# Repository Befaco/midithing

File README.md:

# MIDI Thing v2.2
Firmware for the [Befaco](http://befaco.org) Eurorack MIDI module (MIDI Thing).

## Requirements
You need Arduino >= 1.6.3. 

Additionally you will need the following libraries installed (see the [Arduino Guide](https://www.arduino.cc/en/Guide/Libraries) on how to do this):

* [Bounce2](https://github.com/thomasfredericks/Bounce2) 
* [mcp4728](https://storage.googleapis.com/google-code-archive-downloads/v2/code.google.com/neuroelec/mcp4728_library_v1.3_for_Arduino_1.0.zip)

The [MIDI library](https://github.com/FortySevenEffects/arduino_midi_library) (5.0.2) is bundled in `firmware/src/MIDI`, with a fix for a parser lockup that is not in any upstream release. No need to install it.

## bug fix

- Fixed Retrigger issues
- Fixed Perc trigger note error.

## Uploading the firmware

1. Get an ICSP Programmer 
We normally use an USBasp programmer like this one https://www.ebay.com/itm/USBASP-USB-ISP-Programmer-for-Atmel-AVR-ATMega328-ATMega32U4-Arduino-/322662323277

2. Download Arduino IDE
Go to the official Arduino website https://www.arduino.cc/en/Main/Software and download the latest version of Arduino IDE for your operating system and install it.

3. Download the firmware 
Go to https://github.com/Befaco/midithing and press "clone or download" to download the repository to your computer. Extract the zip file and copy "firmware" folder to your sketchbook folder. 

4. Install the libraries
Download the libraries from Library manager (Bounce2) and install them following the instructions from this link https://www.arduino.cc/en/Guide/Libraries
Keep in mind MCP library must be installed from the following link. Do not use library manager one:
 https://code.google.com/archive/p/neuroelec/downloads 
 
5. Connecting the module
Connect the programmer to the ICSP conector in the back of the module. Pay special attention to the pinout when you plug the module. You can check this link for more information about ICSP https://www.arduino.cc/en/Tutorial/ArduinoISP

6. Upgrading
Press "Open" and search the file "firmware.ino" located on the "firmware" folder. Select "Tools > Board > Arduino/Genuino Uno". Go to "Sketch" and hit "Upload using programmer".

If everything goes well you should see a "Done uploading" message in a few seconds. If something happens during the upgrade, check your Arduino settings following the instructions of this link https://www.arduino.cc/en/Guide/Troubleshooting

## Credits

MIDI Thing firmware v1 was coded with love by Sergio Retamero:
sergio.retamero@gmail.com

Performance boost, bug fixing and extra awesomeness by Jeremy Bernstein:
jeremy.d.bernstein@googlemail.com

Firmware v2 coding:

Quad Polyphonic modes were implemented by Jeremy Bernstein.

New configuration system, duophonic modes implementation, clock modes, a touch of beauty to the interface and a gazillion little details no living person could ever imagine by Alberto "Numeríco" Navarro:
albertonafu@gmail.com 

Calibration method inspired on Mutable instruments CVpal.

Thanks to everyone that took the time to finger point bugs, provide feedback and made loads of  suggestions. Special thanks to Jonatan "Jessica Fletcher" Bernabeu.

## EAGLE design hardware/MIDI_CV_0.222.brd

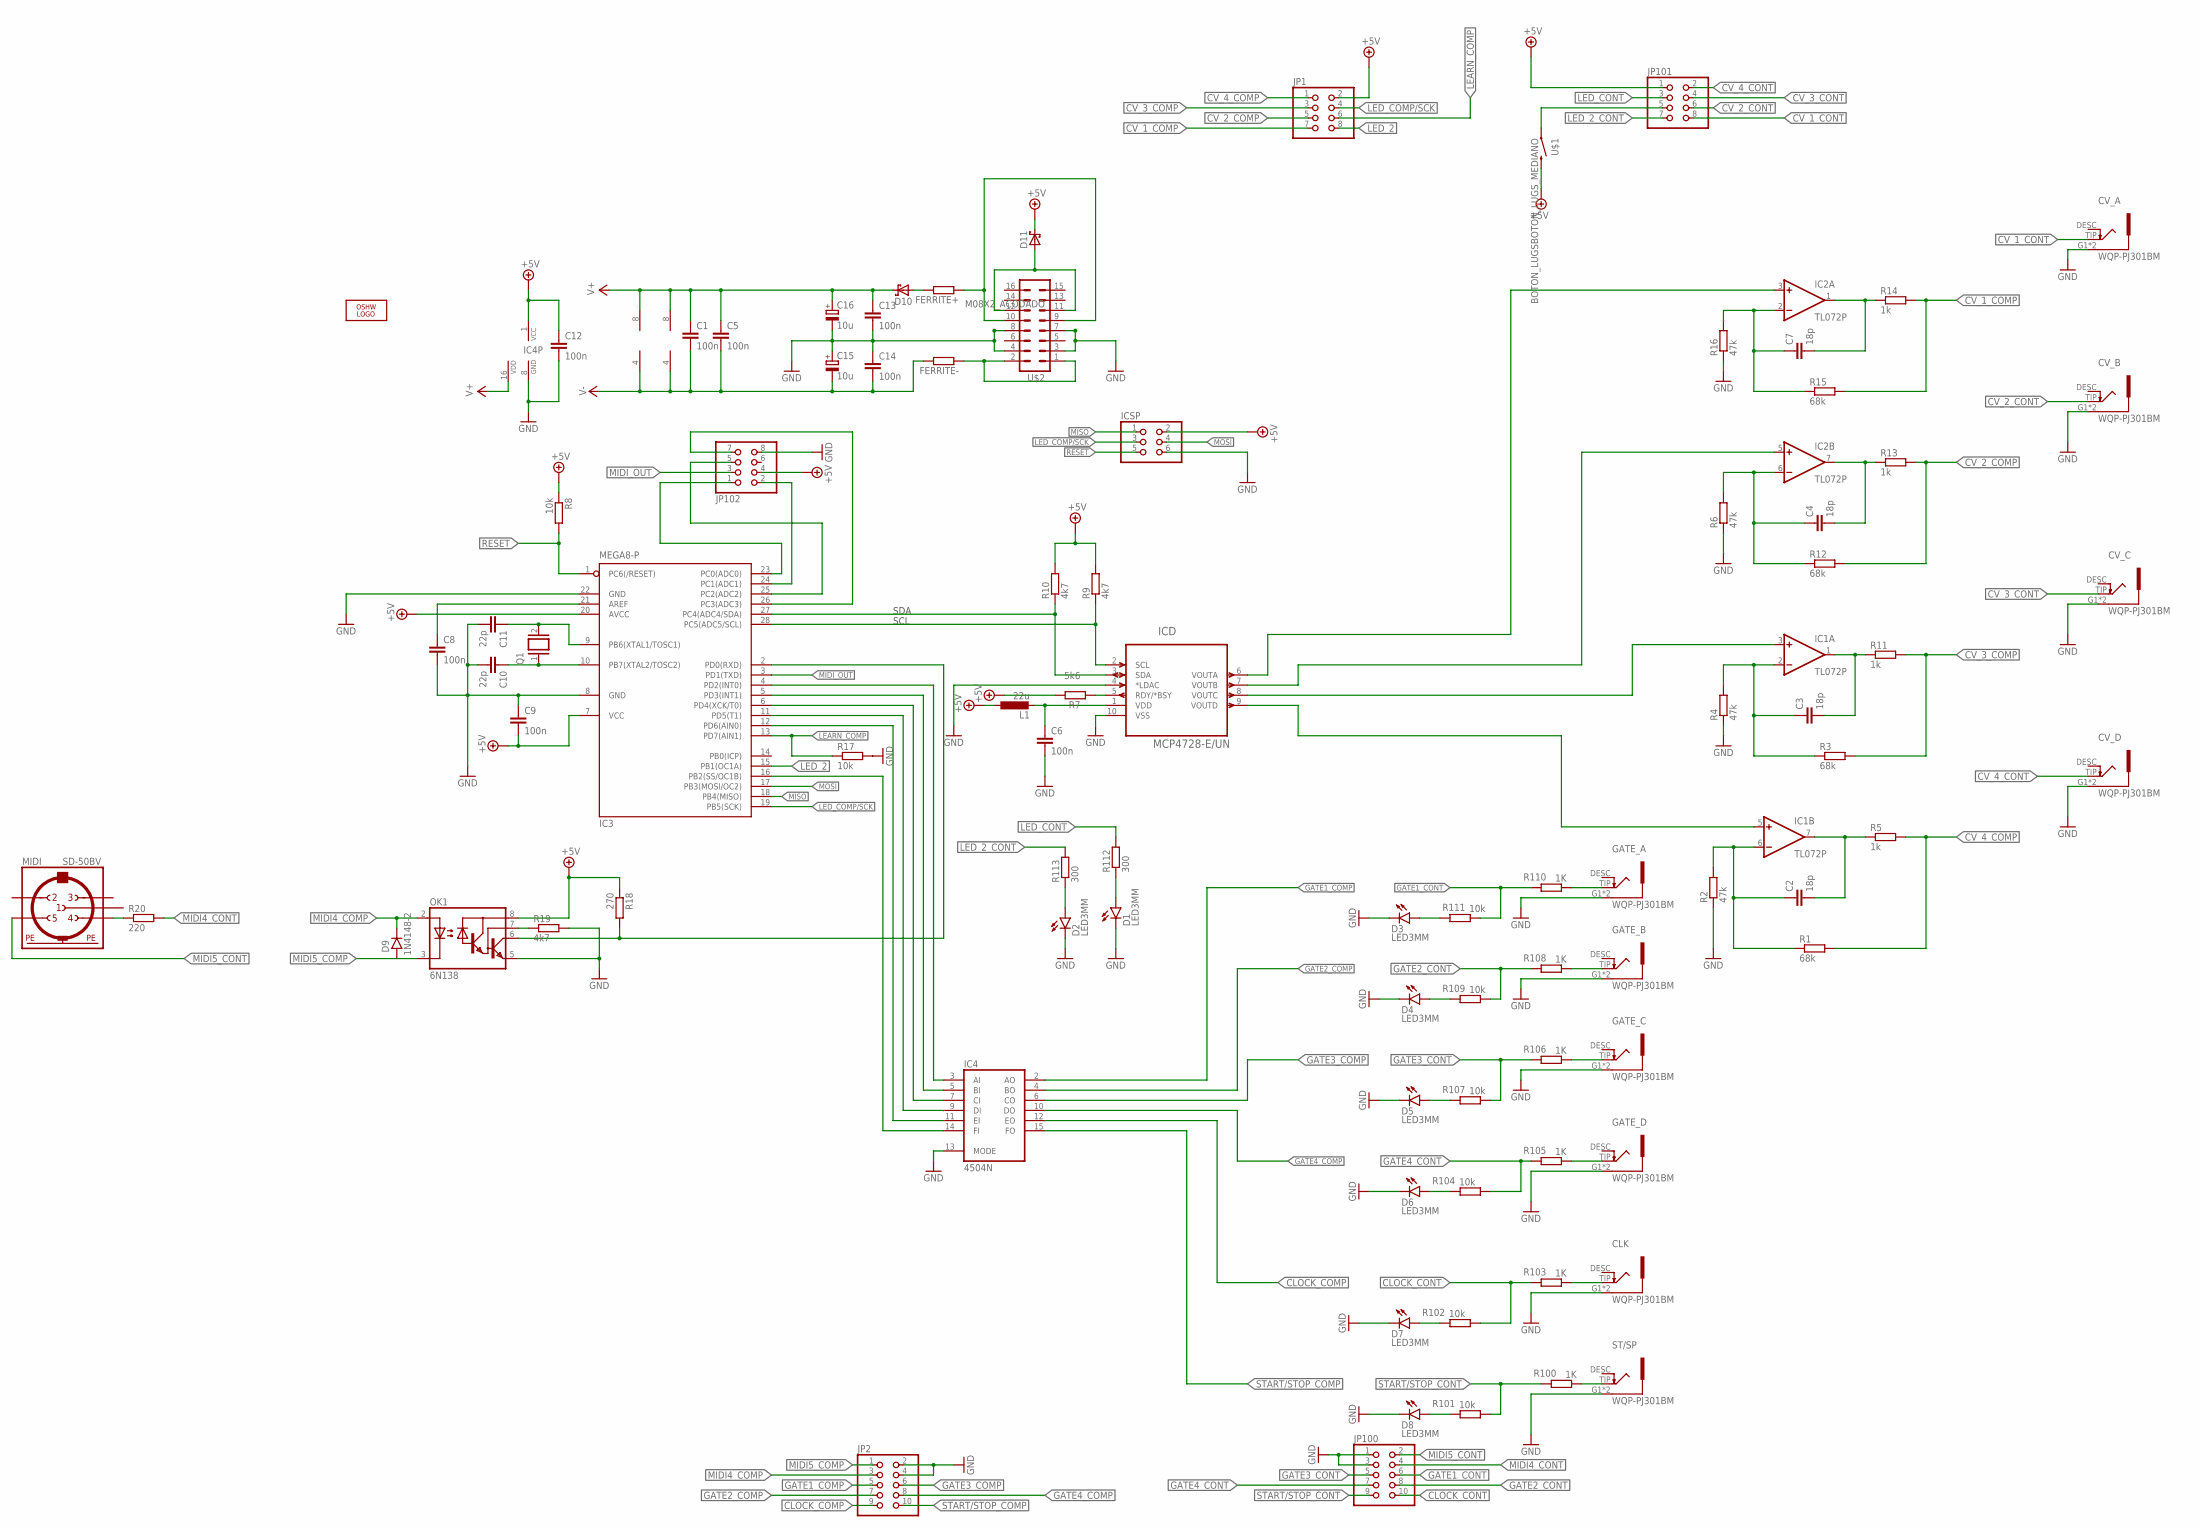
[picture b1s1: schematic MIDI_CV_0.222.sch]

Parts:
$1_35_$: OSHW_LOGO_FILLX0200-NT; OSHW_FILLX200_NOTEXT
C1, C5, C6, C8, C9, C12, C13, C14: 100n; C050-025X075
C2, C3, C4, C7: 18p; C050-025X075
C10, C11: 22p; C050-025X075
C15, C16: 10u; E2-4
CLK: WQP-PJ301BM
CV_A: WQP-PJ301BM
CV_B: WQP-PJ301BM
CV_C: WQP-PJ301BM
CV_D: WQP-PJ301BM
D1, D2, D3, D4, D5, D6, D7, D8: LED3MM
D9: 1N4148-2; DO35-2
D10, D11: SCHOTTKY-DIODEDO35-7; DO35-7
FERRITE+: R-EU_0204/5; 0204/5
FERRITE-: R-EU_0204/5; 0204/5
GATE_A: WQP-PJ301BM
GATE_B: WQP-PJ301BM
GATE_C: WQP-PJ301BM
GATE_D: WQP-PJ301BM
IC1, IC2: TL072P; DIL08
IC3: MEGA8-P; DIL28-3
IC4: 4504N; DIL16
ICD: MCP4728-E/UN; SOP50P490X110-10N
ICSP: PINHD-2X3; 2X03
JP1, JP101, JP102: PINHD-2X4; 2X04
JP2, JP100: PINHD-2X5; 2X05
L1: 22u; 0204/7
MIDI: SD-50BV
OK1: 6N138; DIL08
Q1: XTAL/S; QS
R1, R3, R12, R15: 68k; 0204/5
R2, R4, R6, R16: 47k; 0204/5
R5, R11, R13, R14: 1k; 0204/5
R7: 5k6; 0204/5
R8, R17, R101, R102, R104, R107, R109, R111: 10k; 0204/5
R9, R10, R19: 4k7; 0204/5
R18: 270; 0204/5
R20: 220; 0204/5
R100, R103, R105, R106, R108, R110: 1K; 0204/5
R112, R113: 300; 0204/5
ST/SP: WQP-PJ301BM
U$1: BOTON_LUGSBOTON_LUGS_MEDIANO; BOTON_LUGS_MEDIANO
U$2: M08X2_ACODADO; 2X8-POWER-ACODADO

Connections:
+5V: C9.2, C12.1, D11.C, IC3.7 (VCC), IC3.20 (AVCC), IC4.1 (VCC), ICSP.2, JP1.2, JP101.1, JP102.4, L1.1, OK1.8 (VCC), R7.2, R8.1, R9.2, R10.2, R18.1, U$1.P$2 (2)
A: IC2.3 (+IN), ICD.6 (VOUTA)
B: IC2.5 (+IN), ICD.7 (VOUTB)
C: IC1.3 (+IN), ICD.8 (VOUTC)
CLOCK_COMP: IC4.12 (EO), JP2.9
CLOCK_CONT: JP100.10, R102.1, R103.2
CV_1_COMP: JP1.7, R14.2, R15.2
CV_1_CONT: CV_A.TIP, JP101.8
CV_2_COMP: JP1.5, R12.2, R13.2
CV_2_CONT: CV_B.TIP, JP101.6
CV_3_COMP: JP1.3, R3.2, R11.2
CV_3_CONT: CV_C.TIP, JP101.4
CV_4_COMP: JP1.1, R1.2, R5.2
CV_4_CONT: CV_D.TIP, JP101.2
D: IC1.5 (+IN), ICD.9 (VOUTD)
DAC_A_FEEDBACK_T: C7.2, IC2.1 (OUT), R14.1
GATE1_COMP: IC4.2 (AO), JP2.5
GATE1_CONT: JP100.6, R110.2, R111.1
GATE2_COMP: IC4.4 (BO), JP2.7
GATE2_CONT: JP100.8, R108.2, R109.1
GATE3_COMP: IC4.6 (CO), JP2.6
GATE3_CONT: JP100.5, R106.2, R107.1
GATE4_COMP: IC4.10 (DO), JP2.8
GATE4_CONT: JP100.7, R104.1, R105.2
GND: C6.2, C8.2, C9.1, C10.2, C11.2, C12.2, C13.2, C14.1, C15.+, C16.-, CLK.G1 (SLEVE), CLK.G2 (SLEVE), CV_A.G1 (SLEVE), CV_A.G2 (SLEVE), CV_B.G1 (SLEVE), CV_B.G2 (SLEVE), CV_C.G1 (SLEVE), CV_C.G2 (SLEVE), CV_D.G1 (SLEVE), CV_D.G2 (SLEVE), D1.K (C), D2.K (C), D3.K (C), D4.K (C), D5.K (C), D6.K (C), D7.K (C), D8.K (C), GATE_A.G1 (SLEVE), GATE_A.G2 (SLEVE), GATE_B.G1 (SLEVE), GATE_B.G2 (SLEVE), GATE_C.G1 (SLEVE), GATE_C.G2 (SLEVE), GATE_D.G1 (SLEVE), GATE_D.G2 (SLEVE), IC3.8 (GND), IC3.22 (GND), IC4.8 (GND), IC4.13 (MODE), ICD.4 (*LDAC), ICD.10 (VSS), ICSP.6, JP2.2, JP2.4, JP100.1, JP100.3, JP102.8, OK1.5 (GND), R2.1, R4.1, R6.1, R16.1, R17.2, R19.2, ST/SP.G1 (SLEVE), ST/SP.G2 (SLEVE), U$2.3, U$2.4, U$2.7, U$2.8
LEARN_COMP: IC3.13 (PD7(AIN1)), JP1.6, R17.1
LED_2: IC3.15 (PB1(OC1A)), JP1.8
LED_2_CONT: JP101.7, R113.2
LED_COMP/SCK: IC3.19 (PB5(SCK)), ICSP.3, JP1.4
LED_CONT: JP101.3, R112.2
MIDI4_COMP: D9.C, JP2.3, OK1.2 (A)
MIDI4_CONT: JP100.4, R20.2
MIDI5_COMP: D9.A, JP2.1, OK1.3 (C)
MIDI5_CONT: JP100.2, MIDI.5
MIDI_OUT: IC3.3 (PD1(TXD)), JP102.3
MISO: IC3.18 (PB4(MISO)), ICSP.1
MOSI: IC3.17 (PB3(MOSI/OC2)), ICSP.4
unnamed: D7.A, R102.2
unnamed: C10.1, IC3.10 (PB7(XTAL2/TOSC2)), Q1.1
unnamed: FERRITE-.1, U$2.1, U$2.2
unnamed: IC3.23 (PC0(ADC0)), JP102.1
unnamed: C4.2, IC2.7 (OUT), R13.1
unnamed: C2.1, IC1.6 (-IN), R1.1, R2.2
unnamed: D1.A, R112.1
unnamed: JP101.5, U$1.P$1 (1)
unnamed: IC3.16 (PB2(SS/OC1B)), IC4.14 (FI)
unnamed: C3.2, IC1.1 (OUT), R11.1
unnamed: C7.1, IC2.2 (-IN), R15.1, R16.2
unnamed: IC3.24 (PC1(ADC1)), JP102.2
unnamed: R100.1, ST/SP.TIP
unnamed: IC3.25 (PC2(ADC2)), JP102.5
unnamed: C3.1, IC1.2 (-IN), R3.1, R4.2
unnamed: CLK.TIP, R103.1
unnamed: GATE_D.TIP, R105.1
unnamed: ICD.5 (RDY/*BSY), R7.1
unnamed: IC3.5 (PD3(INT1)), IC4.5 (BI)
unnamed: IC3.26 (PC3(ADC3)), JP102.7
unnamed: C2.2, IC1.7 (OUT), R5.1
unnamed: D11.A, U$2.11, U$2.12
unnamed: IC3.11 (PD5(T1)), IC4.9 (DI)
unnamed: D10.A, FERRITE+.2
unnamed: D2.A, R113.1
unnamed: GATE_A.TIP, R110.1
unnamed: C6.1, ICD.1 (VDD), L1.2
unnamed: C11.1, IC3.9 (PB6(XTAL1/TOSC1)), Q1.2
unnamed: IC3.12 (PD6(AIN0)), IC4.11 (EI)
unnamed: FERRITE+.1, U$2.9, U$2.10
unnamed: D3.A, R111.2
unnamed: D8.A, R101.2
unnamed: GATE_B.TIP, R108.1
unnamed: IC3.4 (PD2(INT0)), IC4.3 (AI)
unnamed: GATE_C.TIP, R106.1
unnamed: D4.A, R109.2
unnamed: IC3.6 (PD4(XCK/T0)), IC4.7 (CI)
unnamed: MIDI.4, R20.1
unnamed: C8.1, IC3.21 (AREF)
unnamed: D5.A, R107.2
unnamed: D6.A, R104.2
unnamed: OK1.7 (VB), R19.1
unnamed: IC3.2 (PD0(RXD)), OK1.6 (VO), R18.2
unnamed: C4.1, IC2.6 (-IN), R6.2, R12.1
RESET: IC3.1 (PC6(/RESET)), ICSP.5, R8.2
SCL_B: IC3.28 (PC5(ADC5/SCL)), ICD.2 (SCL), R9.1
SDA_T: IC3.27 (PC4(ADC4/SDA)), ICD.3 (SDA), R10.1
START/STOP_COMP: IC4.15 (FO), JP2.10
START/STOP_CONT: JP100.9, R100.2, R101.1
V+: C1.1, C5.1, C13.1, C16.+, D10.C, IC1.8 (V+), IC2.8 (V+), IC4.16 (VDD)
V-: C1.2, C5.2, C14.2, C15.-, FERRITE-.2, IC1.4 (V-), IC2.4 (V-)

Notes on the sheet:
SDA
SCL

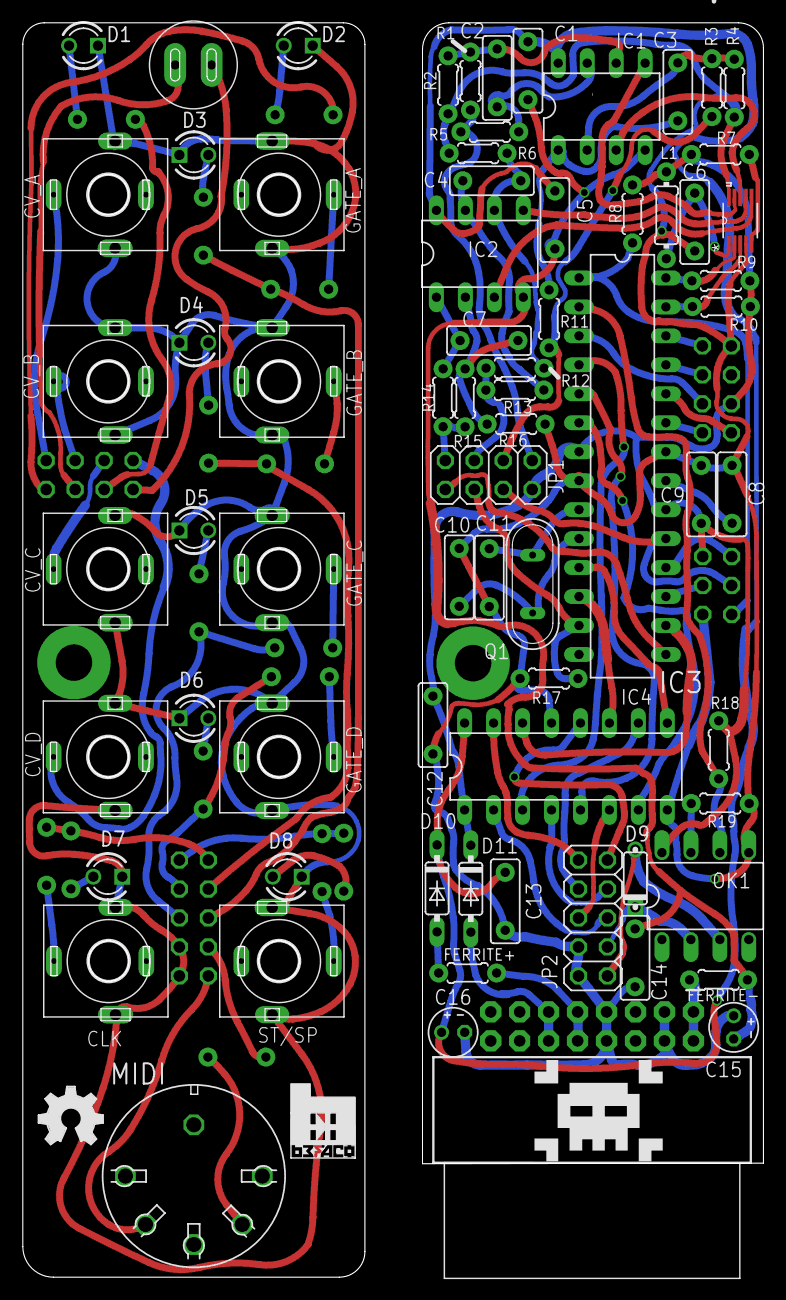
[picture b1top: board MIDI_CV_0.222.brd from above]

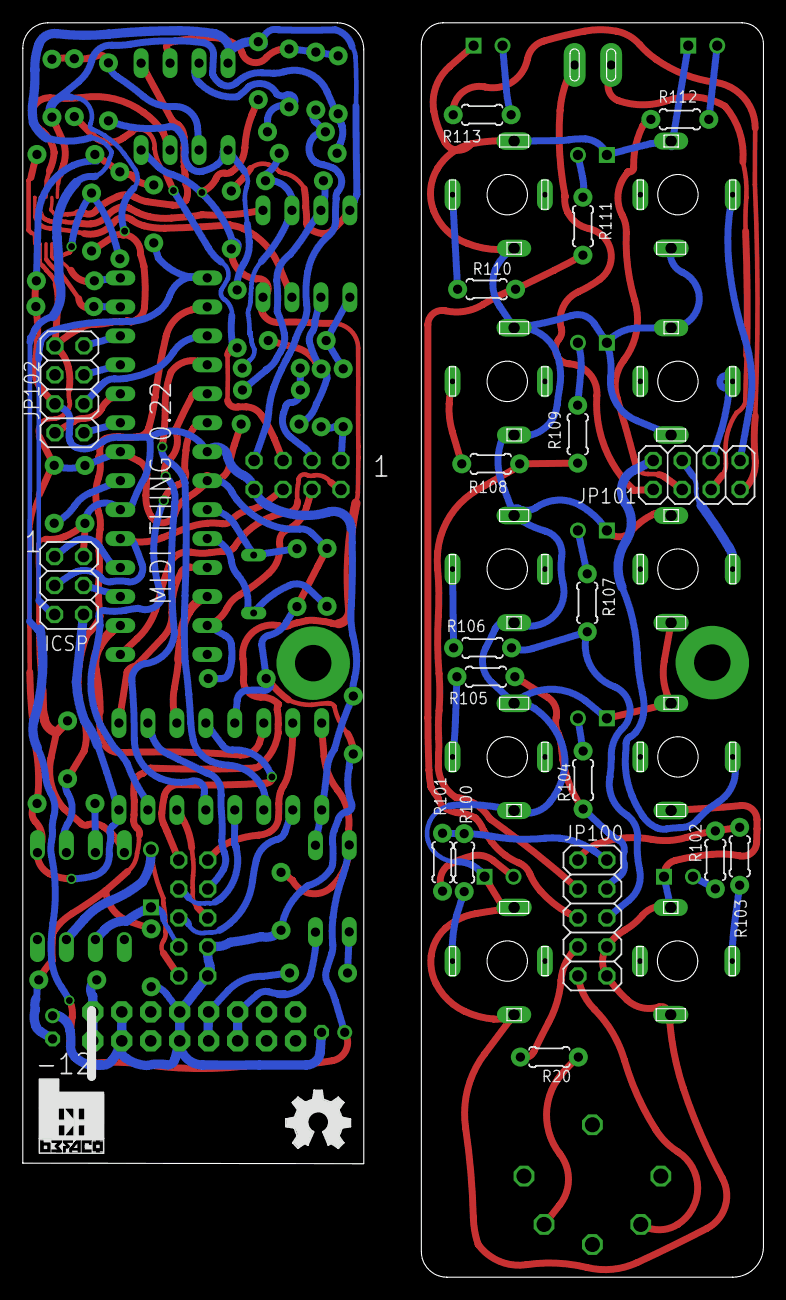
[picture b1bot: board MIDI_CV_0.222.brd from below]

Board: 2 copper layers, 64.9 x 110.0 mm, 95 parts (21 on the bottom side), 88 nets.

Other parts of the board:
LOGO1: OSHW_LOGO_FILLX0200-NT; OSHW_FILLX200_NOTEXT
U$3, U$100: LOGOBEFACOCONLETRAS; LOGOBEFACOCONLETRAS_2
U$4: CALAVERA

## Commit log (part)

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2015-04-13 Adding README.md
2015-04-13 Adding libraries, firmware and README
2015-04-15 Release and debug versions
    Create folders for release and debug versions
2016-01-18 MIDI library updated to v4.2 (maybe this should be a submodule, as the source code is also hosted on Github)
2016-01-18 updated firmware 18 Jan 2015 (contains speed improvement for note events + some reformatting)
2016-01-18 remove firmware debug folder, which contains duplicates. Using #ifdefs to switch debugging on and off is fine and simplifies the repository.
2016-01-19 Added Release Candidate hardware design
2016-01-22 midiclass: minor change for efficiency
2016-01-22 fix some file modes
2016-01-22 more reformatting
2016-01-22 rename ArdMIDItoCVMulti1.ino to firmware.ino so that it can be opened from the repository folder
2016-01-24 README.md: Updating requirements and naming.
2016-01-24 Made few fixes:
    - Velocity value now will stay until next note arrives. Previously it dropped to 0 when note off arrived.
    - Removed clock and ST/SP from drum mode. Now this mode has eight trigger outs so clock and ST/SP will work as usual.
    - Changed clock, trigger and drum trigger length so they won't stay high on higher speeds.
2016-02-05 adding rudimentary .gitignore
2016-02-05 update to Bounce2 library (you'll need to add it to your Arduino library path)
2016-02-05 improve data structure for playing notes (now using a 128-bit field, saving a ton of memory
2016-02-05 minor fix for previous change to bouncer code (prevented leaving cali mode by pressing the button)
2016-02-21 remove reference to non-existent glide function.
2016-02-21 increase calibration mode timeout to 2 minutes (55 seconds is very short)
2016-02-21 initial implementation of portamento ramps (for now, just enable with CC#65, we can implement a time or depth using CC#5 later
2016-02-21 use round() when calculating DAC scaling
2016-02-21 formatting
2016-09-13 refactor note code into a more compact class
2016-09-14 initial polyphony mode
2016-09-14 minor cleanup, fix readMIDIeeprom to not reset the eeprom if a poly mode is selected (ugh).
2016-09-16 move limits include to bitfield header
2016-09-16 ensure that there are only MAXNOTES per channel
2016-09-16 more cleanup & consolidation
2016-09-16 cleanup and renaming
2016-09-19 leave the pool/playing stuff alone unless we're in poly mode
2017-02-08 Created development branch. Duophonic mode, led activty and bug fix added. See Version notes.md
2017-02-08 version changes file added
2017-02-08 Edited versions file.
2017-03-21 Added clock divisions and legatto/retrigger mode. see Version notes.md for further details.
2017-03-21 Deleted unnecesary files.
2017-03-21 Reformating file
2017-03-21 Reformating one more time.
2017-03-23 changed retrigger delay time. Commented code. Reformat version notes file.
2017-03-29 Implented change to solve issue #8. Narrowed clock setups to 5. Refer to version changes file.
2017-04-07 Calibration problems fixed.
2017-04-10 Fixed bug for issue #6 first note no longer ignored
2017-04-29 Calibration was broken. calibrated note was not played.
2017-05-02 Further bug fixing. Version notes changed to reflect new midi channels.
2017-05-19 Further bug fix. added hardware file. Release candidate v2
2018-02-07 RC3. Develop code
2018-03-23 New clock and ST/SP modes added. Learn stored between modes changed. Code optimization and Bug fixing.
2018-04-18 Code commented for final release
2018-04-18 Added updated schematic
2018-04-18 adding updated schematic
2018-04-18 Edited readme file and added user manual.
2018-04-18 Update README.md
    Typos hunting
2018-04-18 Typo hunting
2018-08-14 Fixed ST/SP mode bug
2018-08-16 Edited Readme
2018-12-11 Updated readme.md with bounce2 library link and removed libraries from repo
2018-12-11 Updated user manual to v2
2019-02-26 Add board selection to the upload instructions
    Previously, the instructions were missing the crucial step of selecting the correct board from the Tools > Board menu.
2020-12-01 MIDI library version warning in Readme
2020-12-01 Link to working MIDI library fixed
2020-12-01 Fixed MCP4728 library link
2021-11-09 Fixed bug at Gate 0 output handling
2021-11-09 uploaded old code to compare
2021-11-15 codigo enviado Nov 2021
2021-11-16 Preparing for release
2021-11-23 Set Readme for release
2022-03-16 Round-robin added
    All changes for round-robin are added. I tried to keep the changes to a minimum.. Needs to be testet, preferably by someone else than me.

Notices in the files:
parts and their libraries:
SparkFun: Licensing: CC v3.0 Share-Alike You are welcome to use this library for commercial purposes.
